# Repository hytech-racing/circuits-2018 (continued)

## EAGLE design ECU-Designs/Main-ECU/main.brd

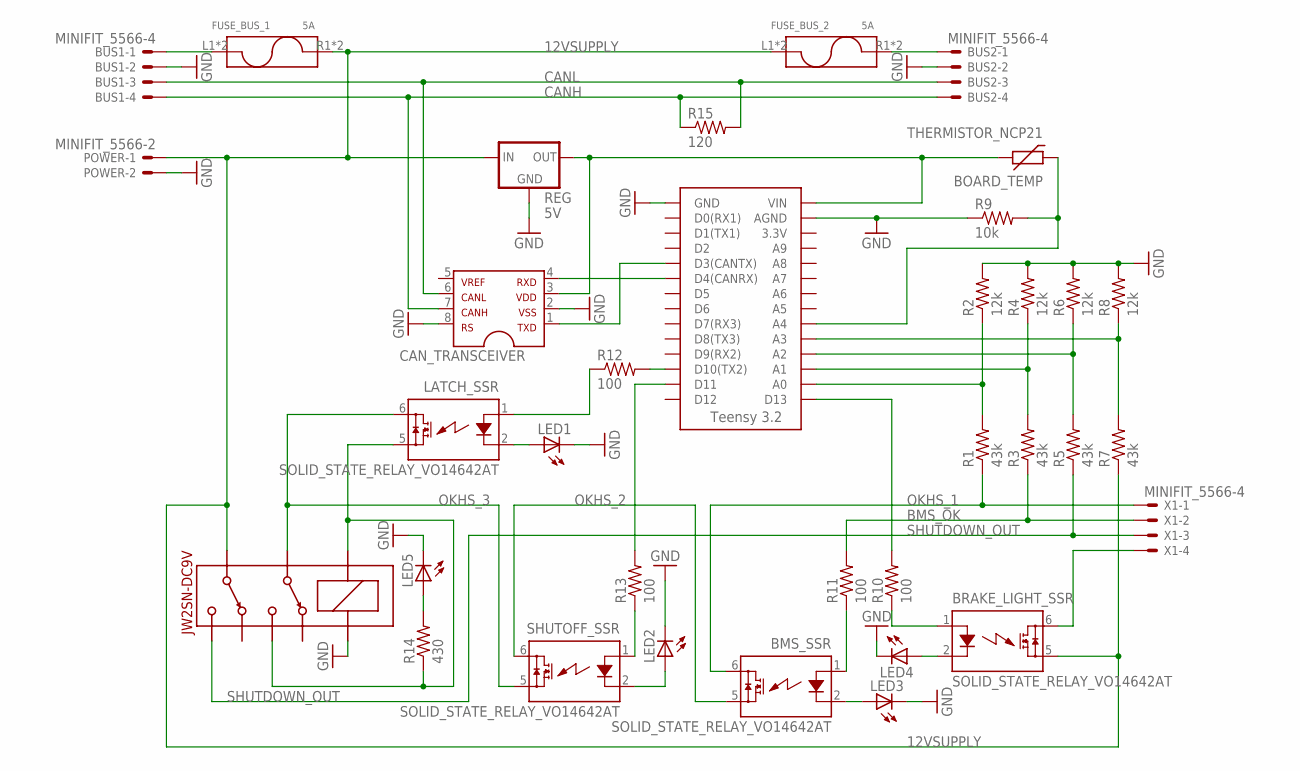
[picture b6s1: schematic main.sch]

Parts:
BMS_SSR: SOLID_STATE_RELAY_VO14642AT; DIL06
BOARD_TEMP: THERMISTOR_NCP21; 0805
BRAKE_LIGHT_SSR: SOLID_STATE_RELAY_VO14642AT; DIL06
BUS1, BUS2: MINIFIT_5566-4
CAN_TRANSCEIVER: MCP2551DIL; DIL08
FUSE_BUS_1, FUSE_BUS_2: 5A; FUSE_HOLDER
IMD_SHUTDOWN: DPDT_RELAY_PANASONIC_JW2SN-DC9V; DPDT_RELAY_PANASONIC_JW2SN
LATCH_SSR: SOLID_STATE_RELAY_VO14642AT; DIL06
LED1, LED2, LED3, LED4, LED5: LED-0805; LED-805
POWER: MINIFIT_5566-2
R1, R3, R5, R7: 43k; 0805
R2, R4, R6, R8: 12k; 0805
R9: 10k; 0805
R10, R11, R12, R13: 100; 0805
R14: 430; 0805
R15: 120; 0805
REG: 5V; SOT223
SHUTOFF_SSR: SOLID_STATE_RELAY_VO14642AT; DIL06
U$3: TEENSY_3.2_SIMPLE
X1: MINIFIT_5566-4

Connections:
5VSUPPLY: BOARD_TEMP.1, CAN_TRANSCEIVER.3, REG.3 (OUT), U$3.VIN
12VSUPPLY: BRAKE_LIGHT_SSR.5 (IO2), FUSE_BUS_1.R1 (2), FUSE_BUS_1.R2 (2), FUSE_BUS_2.L1 (1), FUSE_BUS_2.L2 (1), IMD_SHUTDOWN.6, POWER.1, R7.1, REG.1 (IN)
12VSUPPLY_READ: R7.2, R8.1, U$3.A3
BMS_OK: R3.1, R11.2, X1.2
BMS_OK_READ: R3.2, R4.1, U$3.A1
CANH: BUS1.4, BUS2.4, CAN_TRANSCEIVER.7, R15.1
CANL: BUS1.3, BUS2.3, CAN_TRANSCEIVER.6, R15.2
GND: BUS1.2, BUS2.2, CAN_TRANSCEIVER.2, CAN_TRANSCEIVER.8, IMD_SHUTDOWN.COIL+, LED1.C, LED2.C, LED3.C, LED4.C, LED5.C, POWER.2, R2.2, R4.2, R6.2, R8.2, R9.1, REG.2 (GND), REG.4 (GND), U$3.AGND, U$3.GND
unnamed: LATCH_SSR.2 (LED-), LED1.A
unnamed: CAN_TRANSCEIVER.4, U$3.D4(CANRX)
unnamed: CAN_TRANSCEIVER.1, U$3.D3(CANTX)
unnamed: BRAKE_LIGHT_SSR.6 (IO1), X1.4
unnamed: R12.2, U$3.D10(TX2)
unnamed: IMD_SHUTDOWN.4, IMD_SHUTDOWN.COIL-, LATCH_SSR.5 (IO2), R14.1
unnamed: BRAKE_LIGHT_SSR.2 (LED-), LED4.A
unnamed: LATCH_SSR.1 (LED+), R12.1
unnamed: BMS_SSR.2 (LED-), LED3.A
unnamed: BUS1.1, FUSE_BUS_1.L1 (1), FUSE_BUS_1.L2 (1)
unnamed: BUS2.1, FUSE_BUS_2.R1 (2), FUSE_BUS_2.R2 (2)
unnamed: R13.1, SHUTOFF_SSR.1 (LED+)
unnamed: R10.2, U$3.D13
unnamed: R13.2, U$3.D11
unnamed: BOARD_TEMP.2, R9.2, U$3.A4
unnamed: LED2.A, SHUTOFF_SSR.2 (LED-)
unnamed: BRAKE_LIGHT_SSR.1 (LED+), R10.1
unnamed: BMS_SSR.1 (LED+), R11.1
unnamed: LED5.A, R14.2
OKHS_1: BMS_SSR.6 (IO1), R1.1, X1.1
OKHS_2: BMS_SSR.5 (IO2), SHUTOFF_SSR.6 (IO1)
OKHS_3: IMD_SHUTDOWN.3, LATCH_SSR.6 (IO1), SHUTOFF_SSR.5 (IO2)
OKHS_READ: R1.2, R2.1, U$3.A0
SHUTDOWN_OUT: IMD_SHUTDOWN.5, R5.1, X1.3
SHUTDOWN_OUT_READ: R5.2, R6.1, U$3.A2

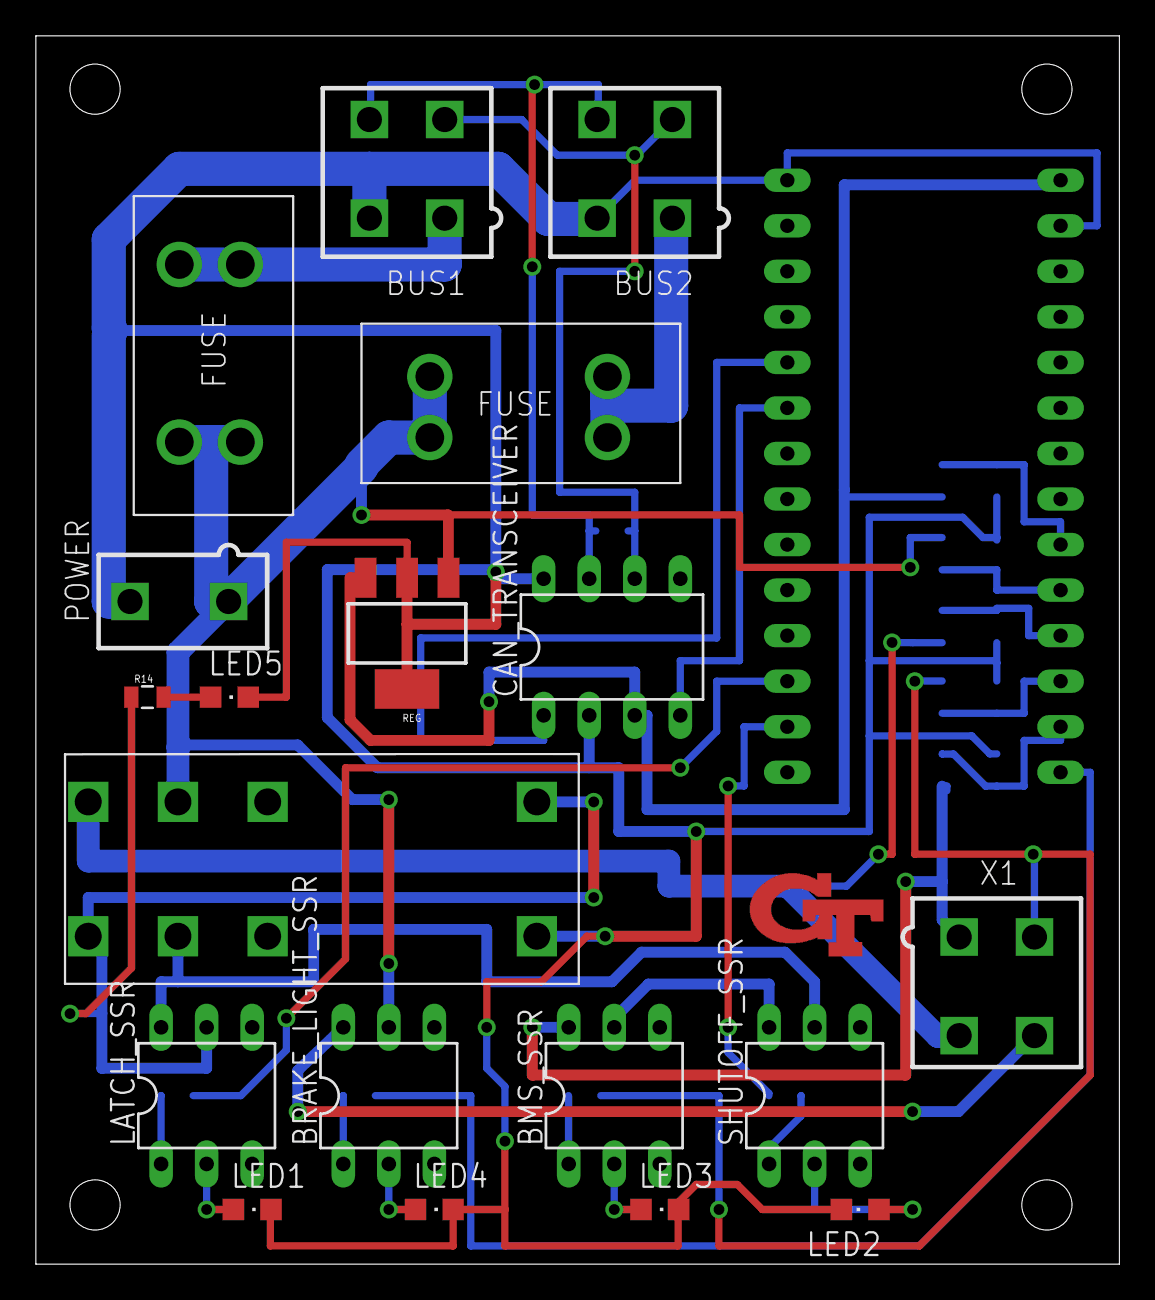
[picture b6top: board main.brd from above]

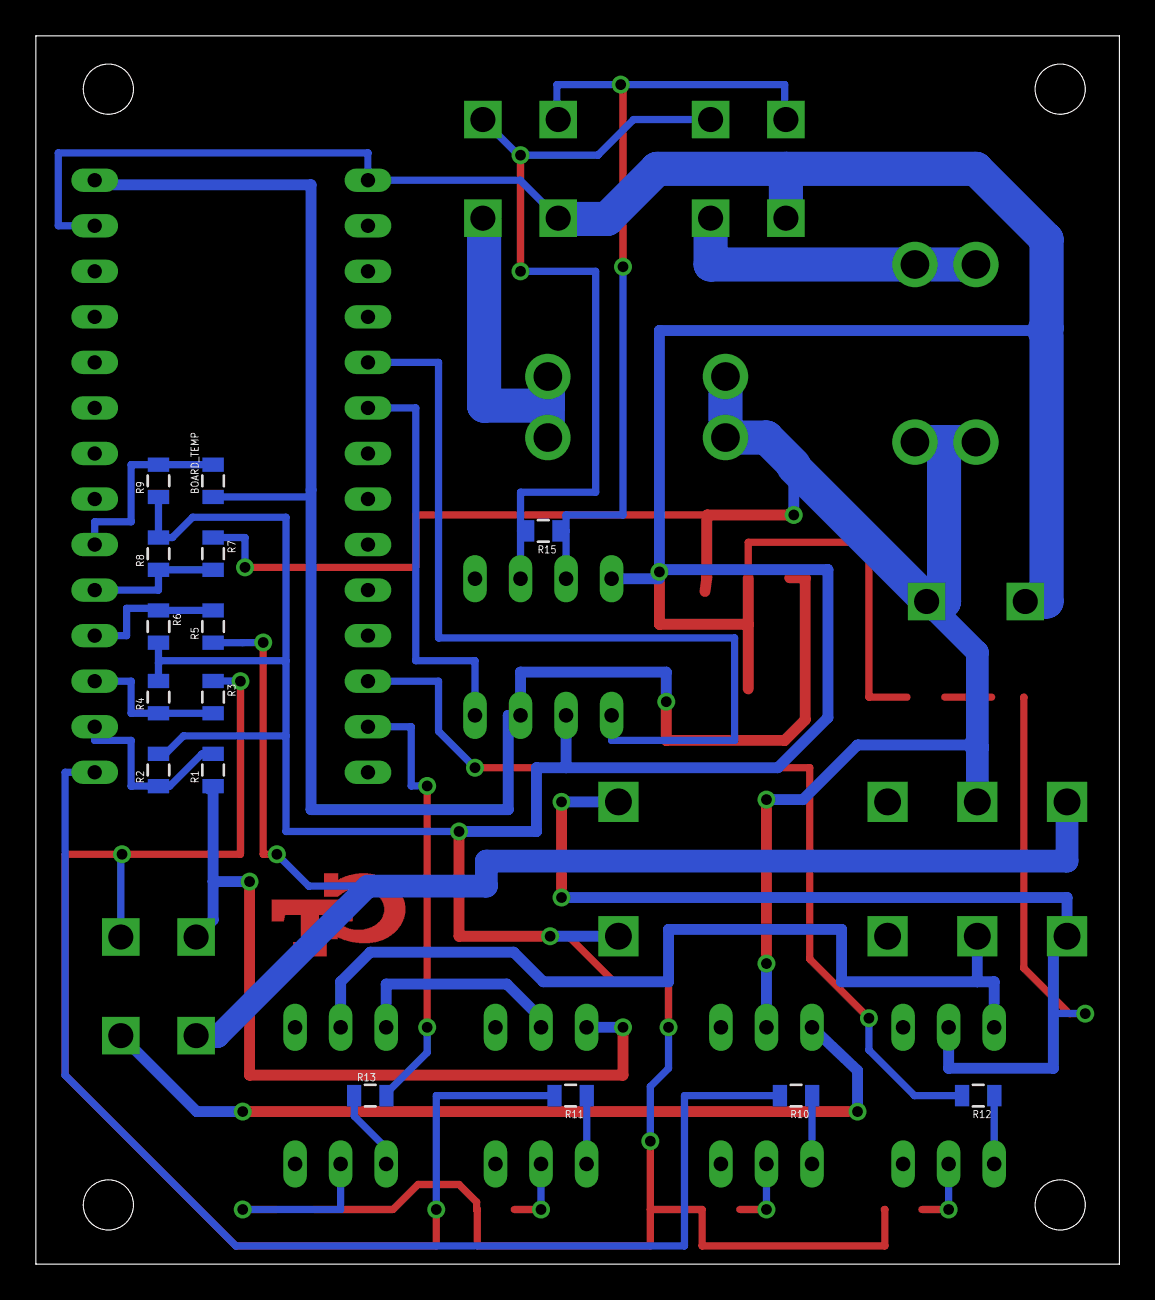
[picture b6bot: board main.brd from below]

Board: 2 copper layers, 60.4 x 68.5 mm, 35 parts (15 on the bottom side), 33 nets.
